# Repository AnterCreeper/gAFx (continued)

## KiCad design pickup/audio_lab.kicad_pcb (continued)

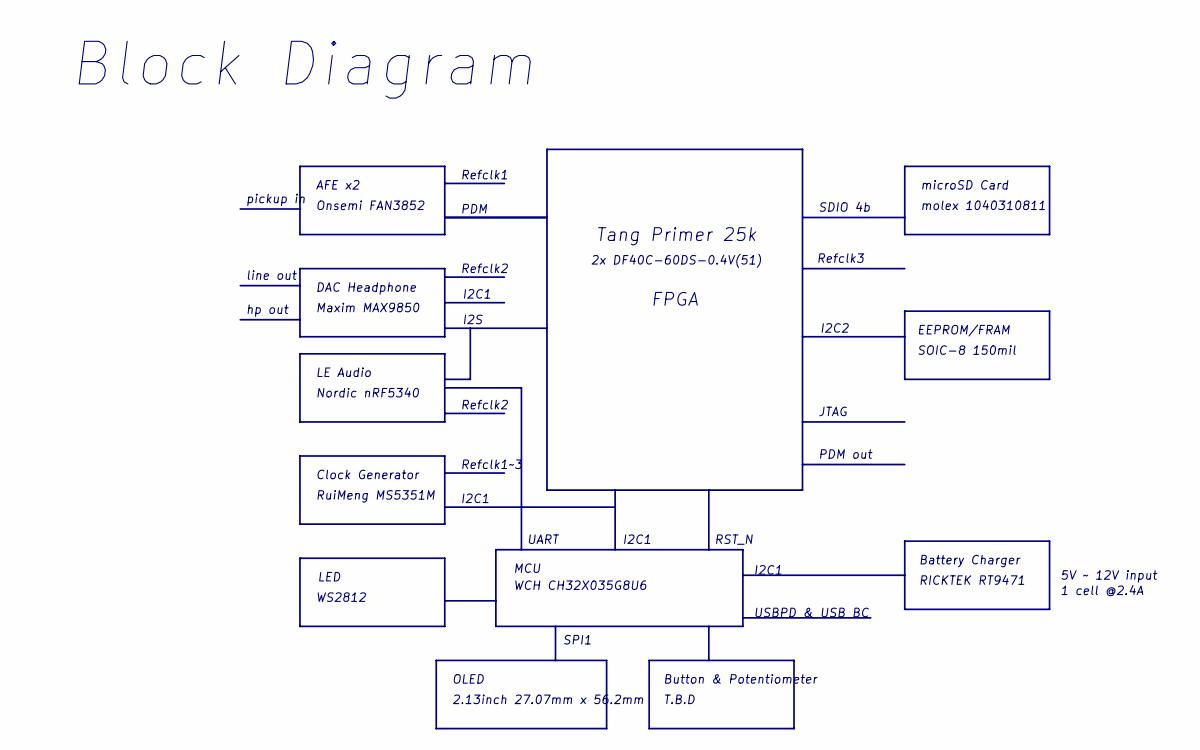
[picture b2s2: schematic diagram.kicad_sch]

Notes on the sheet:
T.B.D
Onsemi FAN3852
Clock Generator
line out
FPGA
PDM out
WCH CH32X035G8U6
5V ~ 12V input
Refclk2
RuiMeng MS5351M
USBPD & USB BC
Refclk3
JTAG
EEPROM/FRAM
Refclk1
I2C1
hp out
WS2812
microSD Card
SOIC-8 150mil
Maxim MAX9850
OLED
RICKTEK RT9471
molex 1040310811
Nordic nRF5340
LE Audio
PDM
Button & Potentiometer
Block Diagram
LED
pickup in
UART
DAC Headphone
I2C2
SDIO 4b
2.13inch 27.07mm x 56.2mm
AFE x2
SPI1
2x DF40C-60DS-0.4V(51)
MCU

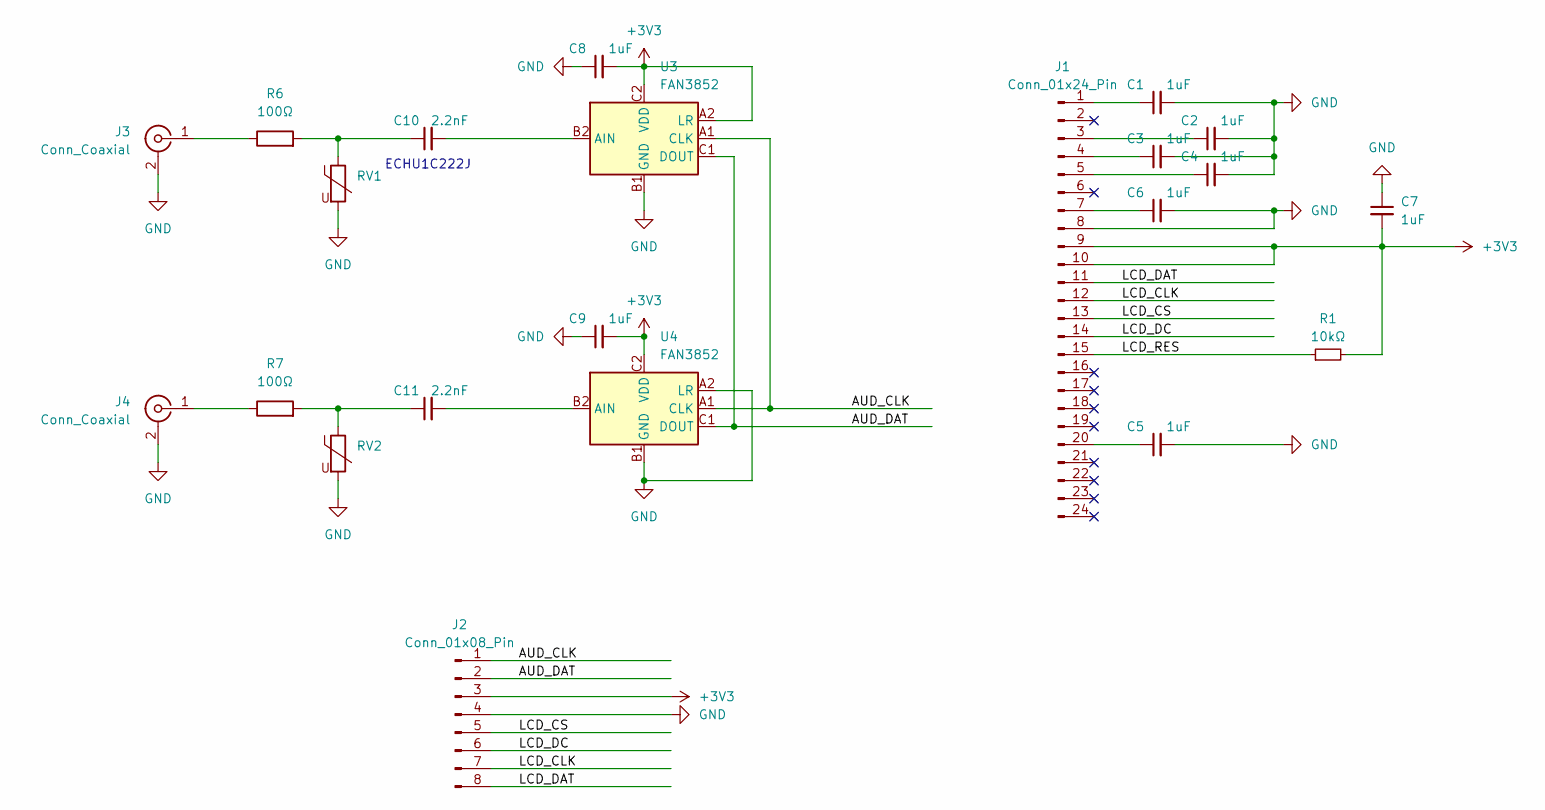
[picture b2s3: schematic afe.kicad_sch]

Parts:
C1, C2, C3, C4, C5, C6, C7, C8, C9: 1uF; C_0402_1005Metric
C10, C11: 2.2nF; C_0603_1608Metric
J1: Conn_01x24_Pin; TE_2-1734839-4_1x24-1MP_P0.5mm_Horizontal
J2: Conn_01x08_Pin; PinSocket_1x08_P1.27mm_Vertical
J3, J4: Conn_Coaxial; IPEX_20449-001E-03
R1: 10kΩ; R_0402_1005Metric
R6, R7: 100Ω; R_0402_1005Metric
RV1, RV2: Varistor; R_0402_1005Metric
U3, U4: FAN3852; Texas_DSBGA-6_0.855x1.255mm_Layout2x3_P0.4mm_LevelC

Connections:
+3V3: C7.2, C8.2, C9.2, J1.9, J1.10, J2.3, R1.2, U3.A2 (LR), U3.C2 (VDD), U4.C2 (VDD)
/AFE/AUD_CLK: J2.1, U3.A1 (CLK), U4.A1 (CLK)
/AFE/AUD_DAT: J2.2, U3.C1 (DOUT), U4.C1 (DOUT)
/AFE/LCD_CLK: J1.12, J2.7
/AFE/LCD_CS: J1.13, J2.5
/AFE/LCD_DAT: J1.11, J2.8
/AFE/LCD_DC: J1.14, J2.6
/AFE/LCD_RES: J1.15, R1.1
GND: C1.2, C2.2, C3.2, C4.2, C5.2, C6.2, C7.1, C8.1, C9.1, J1.8, J1.MP, J2.4, J3.2 (Ext), J4.2 (Ext), RV1.2, RV2.2, U3.3 (GND), U3.B1 (GND), U4.3 (GND), U4.A2 (LR), U4.B1 (GND)
unnamed: C10.1, R6.2, RV1.1
unnamed: C11.1, R7.2, RV2.1
unnamed: C1.1, J1.1
unnamed: C2.1, J1.3
unnamed: C3.1, J1.4
unnamed: C4.1, J1.5
unnamed: C6.1, J1.7
unnamed: C5.1, J1.20
unnamed: J3.1 (In), R6.1
unnamed: J4.1 (In), R7.1
unnamed: C10.2, U3.B2 (AIN)
unnamed: C11.2, U4.B2 (AIN)

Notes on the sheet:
ECHU1C222J

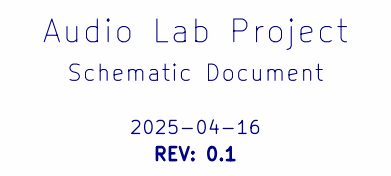
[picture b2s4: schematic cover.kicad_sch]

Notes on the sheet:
2025-04-16
Schematic Document
REV: 0.1
Audio Lab Project

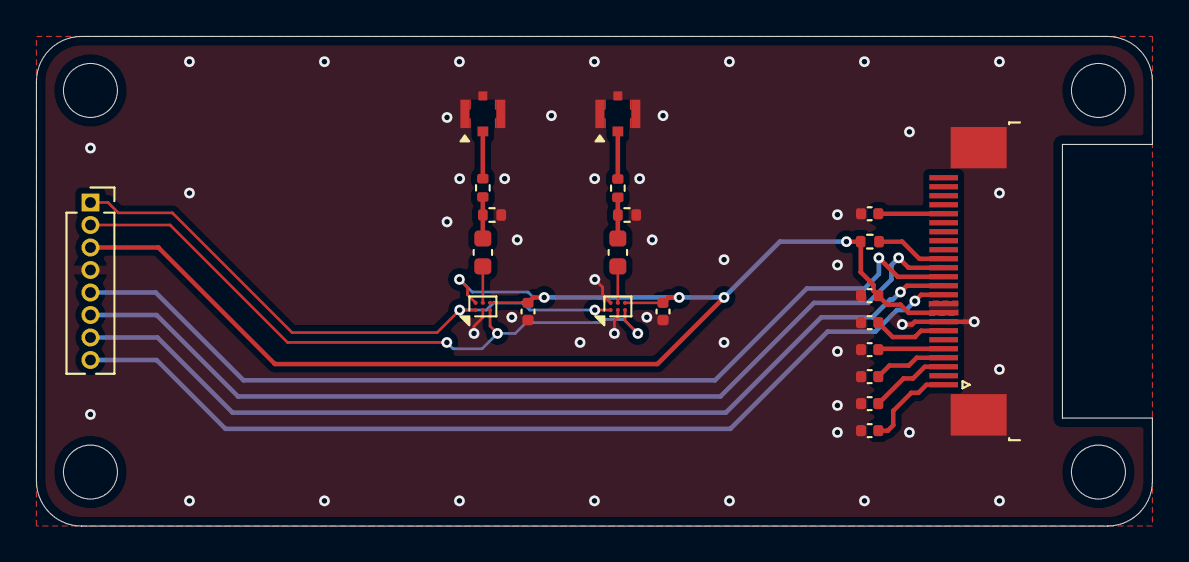
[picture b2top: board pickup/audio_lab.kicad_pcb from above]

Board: 2 copper layers, 62.0 x 27.2 mm, 22 parts (0 on the bottom side), 21 nets.

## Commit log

2025-05-29 Create LICENSE
2025-06-01 upload files
